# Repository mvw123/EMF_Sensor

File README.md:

EMF_Sensor
==========
Brief
-----
This is an open hardware design for an EMF sensor and transmitter circuit (sometimes known as a tone generator and detector, an ELF sensor, warbler or wire follower) which can be used to send a 2kHz audible tone down a wire with the transmitter and sense the presence of the wire with the receiver. It's main uses are for hidden wire and wire boundary detection. 

This is NOT for connection to LIVE mains or hazardous voltages - there are NO safety caps or safety barriers in the circuit. 

The circuit is created with Ki-CAD, an open source EDA tool for schematic capture and PCB layout. There are two boards in the design seperated by a snap off region. One for the transmitter, one for the receiver. The design should be battery powered from a 9v battery for each board.

The circuit is designed so that it can be used for other educational purposes and for general operational amplifier design. 

MVW

Details
-------
The PCB uses a mixture of through hole and SMD 1206 size components. These parts were chosen as a trade off between size and ease of fitting. Through hole axial leaded resistors and capacitors can be soldered onto the 1206 SMD pads if desired by soldering the parts vertically. SMD parts are used to reduce the PCB size which is the most costly part of the design. The PCB could have been smaller, but the aim is to allow beginners to be able to easily solder to the pads as well as experts. 

A Simetrix simulation file is included. Simetrix is a windows simulator which can be downloaded and used freely up to its node limit which is more than adequate for most situations. Please download and tweak it, i think you'll find some components are not entirely needed.

CAD B (Rev 0.02) [WORK IN PROGRESS] March 2014
-----------------------------
Schematic and PCB updated to fix bug stopping the wien bridge oscillator working
schematic and PCB updated to add an inline resistor for the voltage reference for one of the amplifiers
This version was edited using the 7-7-2013 BZR 4022 -stable build for windows which upgrades the PCB to a new type and renames its file extension. 
The Design would benefit from splitting into two seperate designs.
The circuit schematic pages need renaming to something more sensible. 
BOM not available

The design requires external parts not shown on the circuit schematic. eg:-
9v battery 
battery connector
2.5mm earphone adapter
wire - length TBD

CAD A (Rev 0.01) [NOT TESTED] March 2014
-----------------------------
First dev release, not tested - awaiting return of PCBs. 
Known bugs exist. 
The wien bridge oscillator is wired incorrectly.
The oscillator resistor/capacitor values need setting up (board released whilst the values are tweaked)

The board is being produced by oshpark which ships internationally. Price for the minimum 3 boards (in march 2014) is approximately $25

Ki-CAD created schematic, layout, gebers
Simetrix simulation file
BOM needs to be finalised.

Requires external parts not shown on the circuit schematic. eg
9v battery 
battery connector
2.5mm earphone adapter
wire - length TBD

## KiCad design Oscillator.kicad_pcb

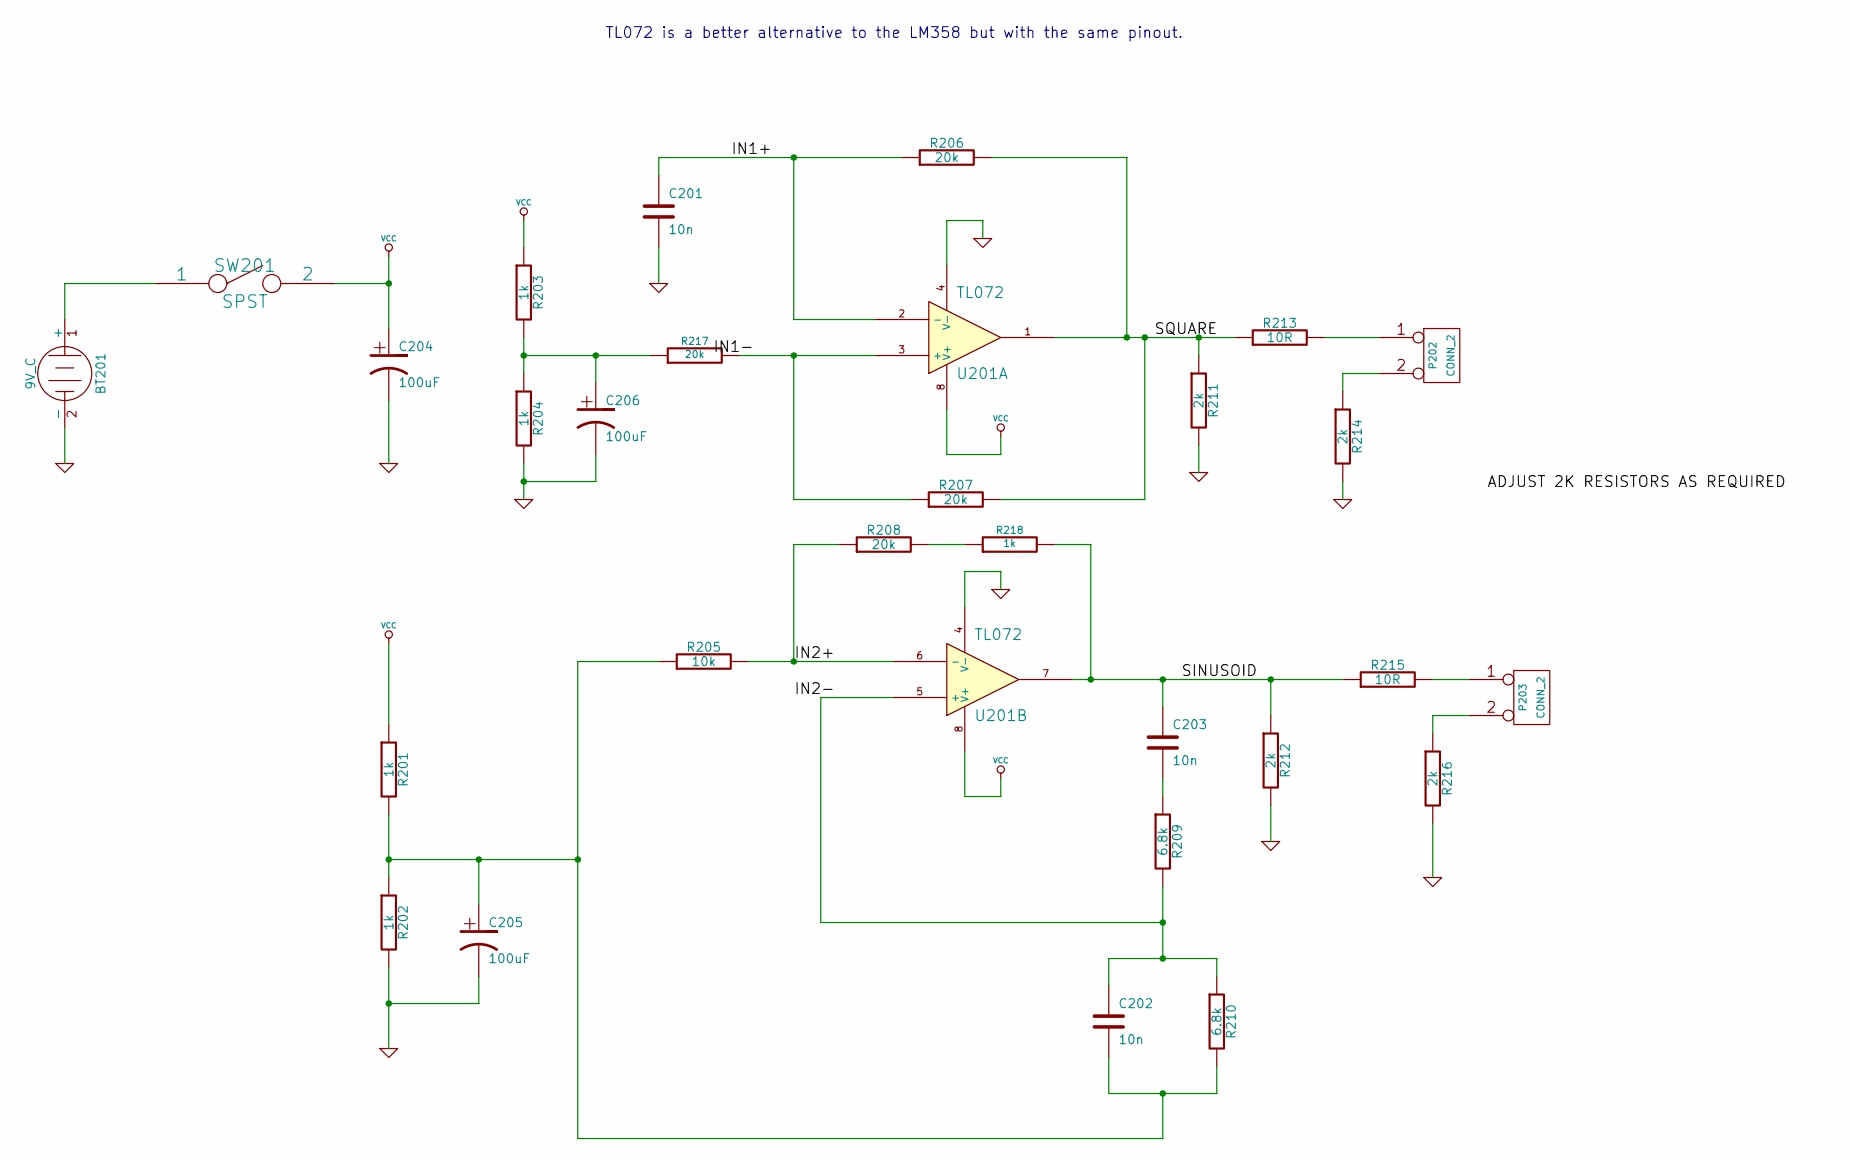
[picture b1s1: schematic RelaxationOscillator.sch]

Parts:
BT201: 9V_C
C201, C202, C203: 10n
C204, C205, C206: 100uF
P202, P203: CONN_2
R201, R202, R203, R204: 1k
R205: 10k
R206, R207, R208: 20k
R209, R210: 6.8k
R211, R212, R214, R216: 2k
R213, R215: 10R
R217: 20k
R218: 1k
SW201: SPST
U201: TL072

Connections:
/RelaxationOscillator/IN1+: C201.1, R206.1, U201.2 (-)
/RelaxationOscillator/IN2+: R205.2, R208.1, U201.6 (-)
/RelaxationOscillator/IN2-: C202.1, R209.2, R210.1, U201.5 (+)
/RelaxationOscillator/SINUSOID: C203.1, R212.1, R215.1, R218.2, U201.7
/RelaxationOscillator/SQUARE: R206.2, R207.2, R211.1, R213.1, U201.1
GND: BT201.2 (-), C201.2, C204.2, C205.2, C206.2, R202.2, R204.2, R211.2, R212.2, R214.2, R216.2, U201.4 (V-); also elsewhere on the board
unnamed: C203.2, R209.1
unnamed: R207.1, R217.2, U201.3 (+)
unnamed: P202.2 (PM), R214.1
unnamed: P203.1, R215.2
unnamed: P203.2 (PM), R216.1
unnamed: R208.2, R218.1
unnamed: C206.1, R203.2, R204.1, R217.1
unnamed: BT201.1 (+), SW201.1
unnamed: P202.1, R213.2
unnamed: C202.2, C205.1, R201.2, R202.1, R205.1, R210.2
VCC: C204.1, R201.1, R203.1, SW201.2, U201.8 (V+)

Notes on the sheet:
TL072 is a better alternative to the LM358 but with the same pinout.

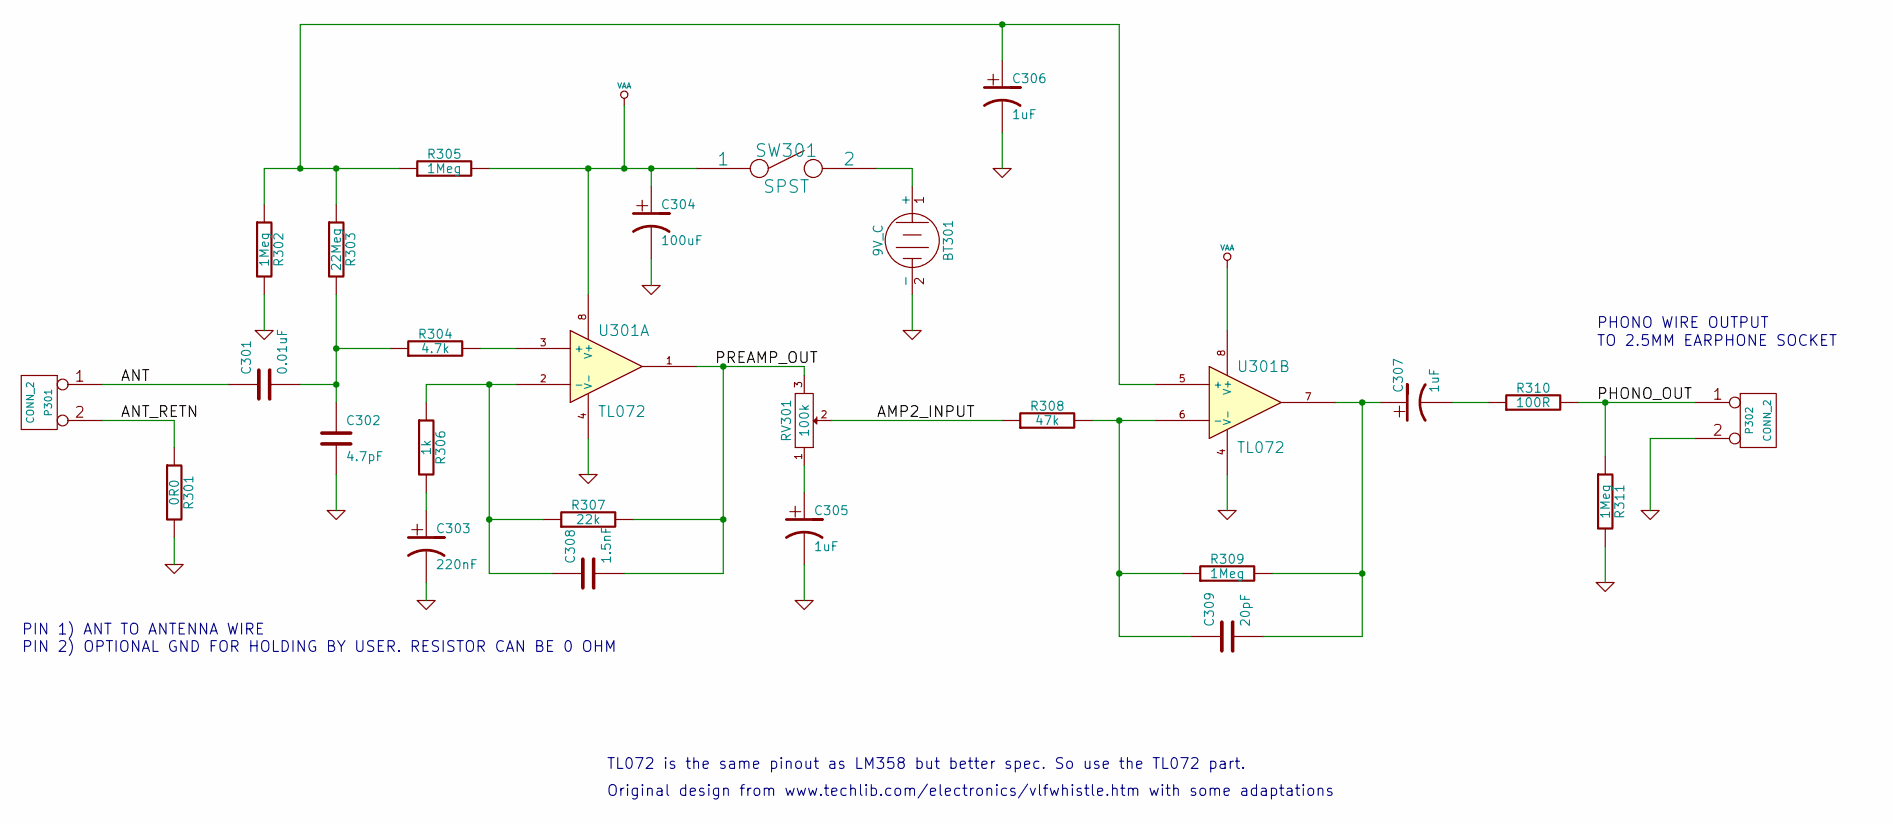
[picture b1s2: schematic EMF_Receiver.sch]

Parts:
BT301: 9V_C
C301: 0.01uF
C302: 4.7pF
C303: 220nF
C304: 100uF
C305, C306, C307: 1uF
C308: 1.5nF
C309: 20pF
P301, P302: CONN_2
R301: 0R0
R302, R305, R309, R311: 1Meg
R303: 22Meg
R304: 4.7k
R306: 1k
R307: 22k
R308: 47k
R310: 100R
RV301: 100k
SW301: SPST
U301: TL072

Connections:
/EMF_Receiver/AMP2_INPUT: R308.1, RV301.2
/EMF_Receiver/ANT: C301.1, P301.1
/EMF_Receiver/ANT_RETN: P301.2 (PM), R301.1
/EMF_Receiver/PHONO_OUT: P302.1, R310.2, R311.1
/EMF_Receiver/PREAMP_OUT: C308.2, R307.2, RV301.3, U301.1
GND: BT301.2 (-), C302.2, C303.2, C304.2, C305.2, C306.2, P302.2 (PM), R301.2, R302.2, R311.2, U301.4 (V-); also elsewhere on the board
unnamed: C305.1, RV301.1
unnamed: C307.2, R310.1
unnamed: C307.1, C309.2, R309.2, U301.7
unnamed: C301.2, C302.1, R303.2, R304.1
unnamed: C303.1, R306.2
unnamed: C306.1, R302.1, R303.1, R305.1, U301.5 (+)
unnamed: R304.2, U301.3 (+)
unnamed: BT301.1 (+), SW301.2
unnamed: C309.1, R308.2, R309.1, U301.6 (-)
unnamed: C308.1, R306.1, R307.1, U301.2 (-)
VAA: C304.1, R305.2, SW301.1, U301.8 (V+)

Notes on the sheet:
PHONO WIRE OUTPUT
TO 2.5MM EARPHONE SOCKET
PIN 1) ANT TO ANTENNA WIRE PIN 2) OPTIONAL GND FOR HOLDING BY USER. RESISTOR CAN BE 0 OHM
Original design from www.techlib.com/electronics/vlfwhistle.htm with some adaptations
TL072 is the same pinout as LM358 but better spec. So use the TL072 part.

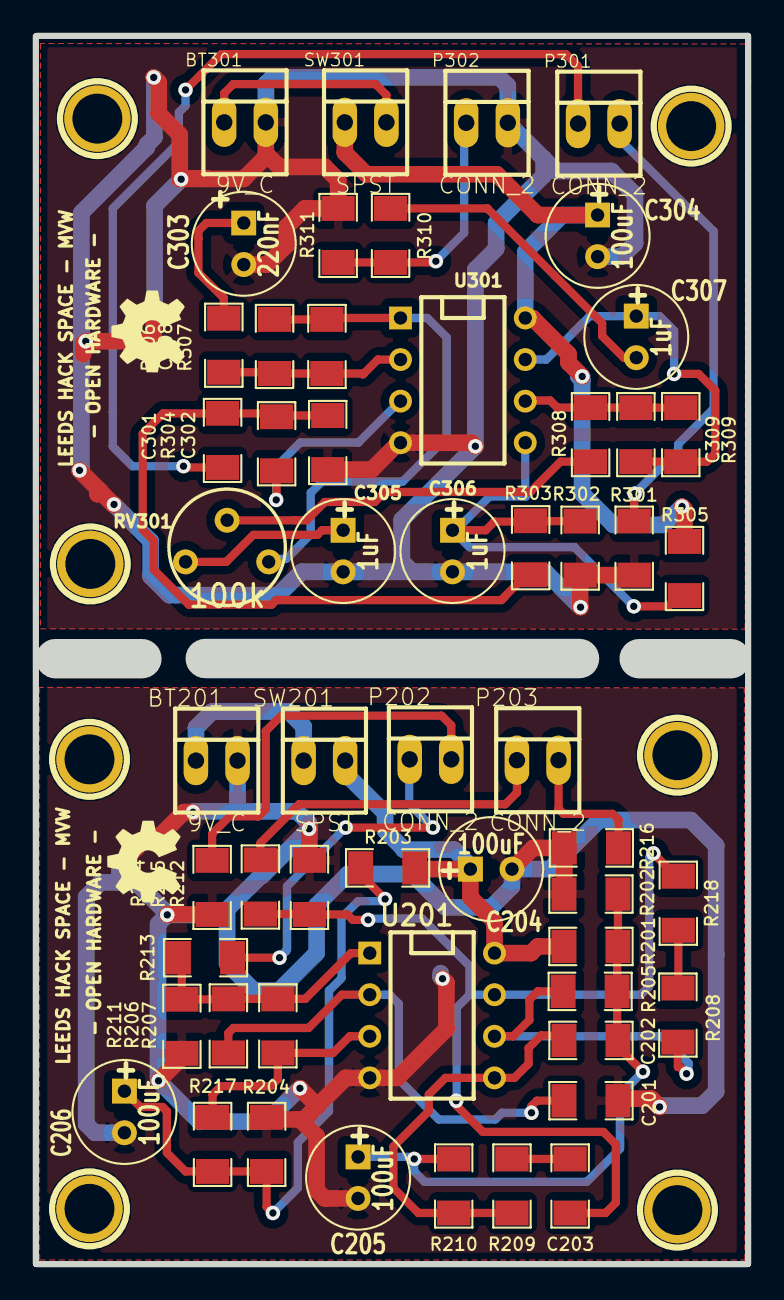
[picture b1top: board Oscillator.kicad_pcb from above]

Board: 2 copper layers, 41.5 x 73.0 mm, 62 parts (0 on the bottom side), 33 nets.

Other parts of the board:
1PIN, 1PIN#2, 1PIN#3, 1PIN#4, 1PIN#5, 1PIN#6, 1PIN#7: P***; 1pin

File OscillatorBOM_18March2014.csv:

ref	value
BT201	9V_C
BT301	9V_C
C201	10n
C202	10n
C203	10n
C204	100uF
C205	100uF
C206	100uF
C301	0.01uF
C302	4.7pF
C303	220nF
C304	100uF
C305	1uF
C306	1uF
C307	1uF
C308	1.5nF
C309	20pF
P202	CONN_2
P203	CONN_2
P301	CONN_2
P302	CONN_2
R201	1k
R202	1k
R203	1k
R204	1k
R205	10k
R206	20k
R207	20k
R208	20k
R209	6.8k
R210	6.8k
R211	2k
R212	2k
R213	10R
R214	2k
R215	10R
R216	2k
R217	20k
R218	1k
R301	0R0
R302	1Meg
R303	22Meg
R304	4.7k
R305	1Meg
R306	1k
R307	22k
R308	47k
R309	1Meg
R310	100R
R311	1Meg
RV301	100k
SW201	SPST
SW301	SPST
U201	TL072
U301	TL072

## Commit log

2014-03-09 testing commit
    testing commit
2014-03-09 First Commit of CAD A released for PCB manufacture
    First commit of the CAD A released for PCB manufacture. Includes the
    gerbers. no BOM is output here since it is liable to change. Also the
    simulation files are not present, they will be added later.
2014-03-09 Added comments about external parts required.
2014-03-09 Added simetrix simulation file for the receiver
    Simulation requires the simetrix simulation software which is available
    freely for the intro version. http://www.simetrix.co.uk Created with v
    7.10. Can be used in windows.
2014-03-10 Clarified description
2014-03-10 corrected typos
2014-03-10 added note about known issues.
2014-03-16 Updated schematic and moved files to new location
    Corrected errors in the schematic which will affect the PCB. PCB not
    changed yet. Updated resistor and cap values and changed amp type to
    comply with the simulations. The CAD A wien-bridge PCB will not
    oscillate. The relaxation oscillator will oscillate but the new values
    are required. The new schematic adds new components to the circuit which
    need putting into the PCB.
2014-03-16 Added notes to schematic pdf. moved a few files around and deleted others
    added notes to the schematic pdf indicating cad A is faulty AND MOVED A
    FEW OUTPUT FILES AROUND
2014-03-16 PCB updated from schema. Using new Kicad version
    Updated the PCB with the schematic updates. Using the newer kicad
    version for windows. 7-7-2013 BZR 4022 -stable
    The old PCB file has been updated to the new version.
2014-03-16 Minor edits and typo corrections
2014-03-16 minor changes
2014-05-02 removed reference to hackspace
2014-05-02 added tone generator and detector description of a device found on maplin.co.uk
    added tone generator and detector description of a device found on maplin.co.uk
    eg the n74cc
    http://www.maplin.co.uk/p/cable-tracker-with-tone-generator-n74cc
2014-05-02 Added note regarding test status in title line
2014-05-02 committing some library updates and sims along with a bom
    committing some library updates and sims along with a bom.
    These were updated quite a while ago so i'm not sure if this information
    is accurate or correct.
2014-05-31 Created pdf of current design
2014-07-28 Added notes to oscillator page. no other changes
    Added notes to oscillator page. no other changes
2014-08-31 few basic updates
    few basic updates
